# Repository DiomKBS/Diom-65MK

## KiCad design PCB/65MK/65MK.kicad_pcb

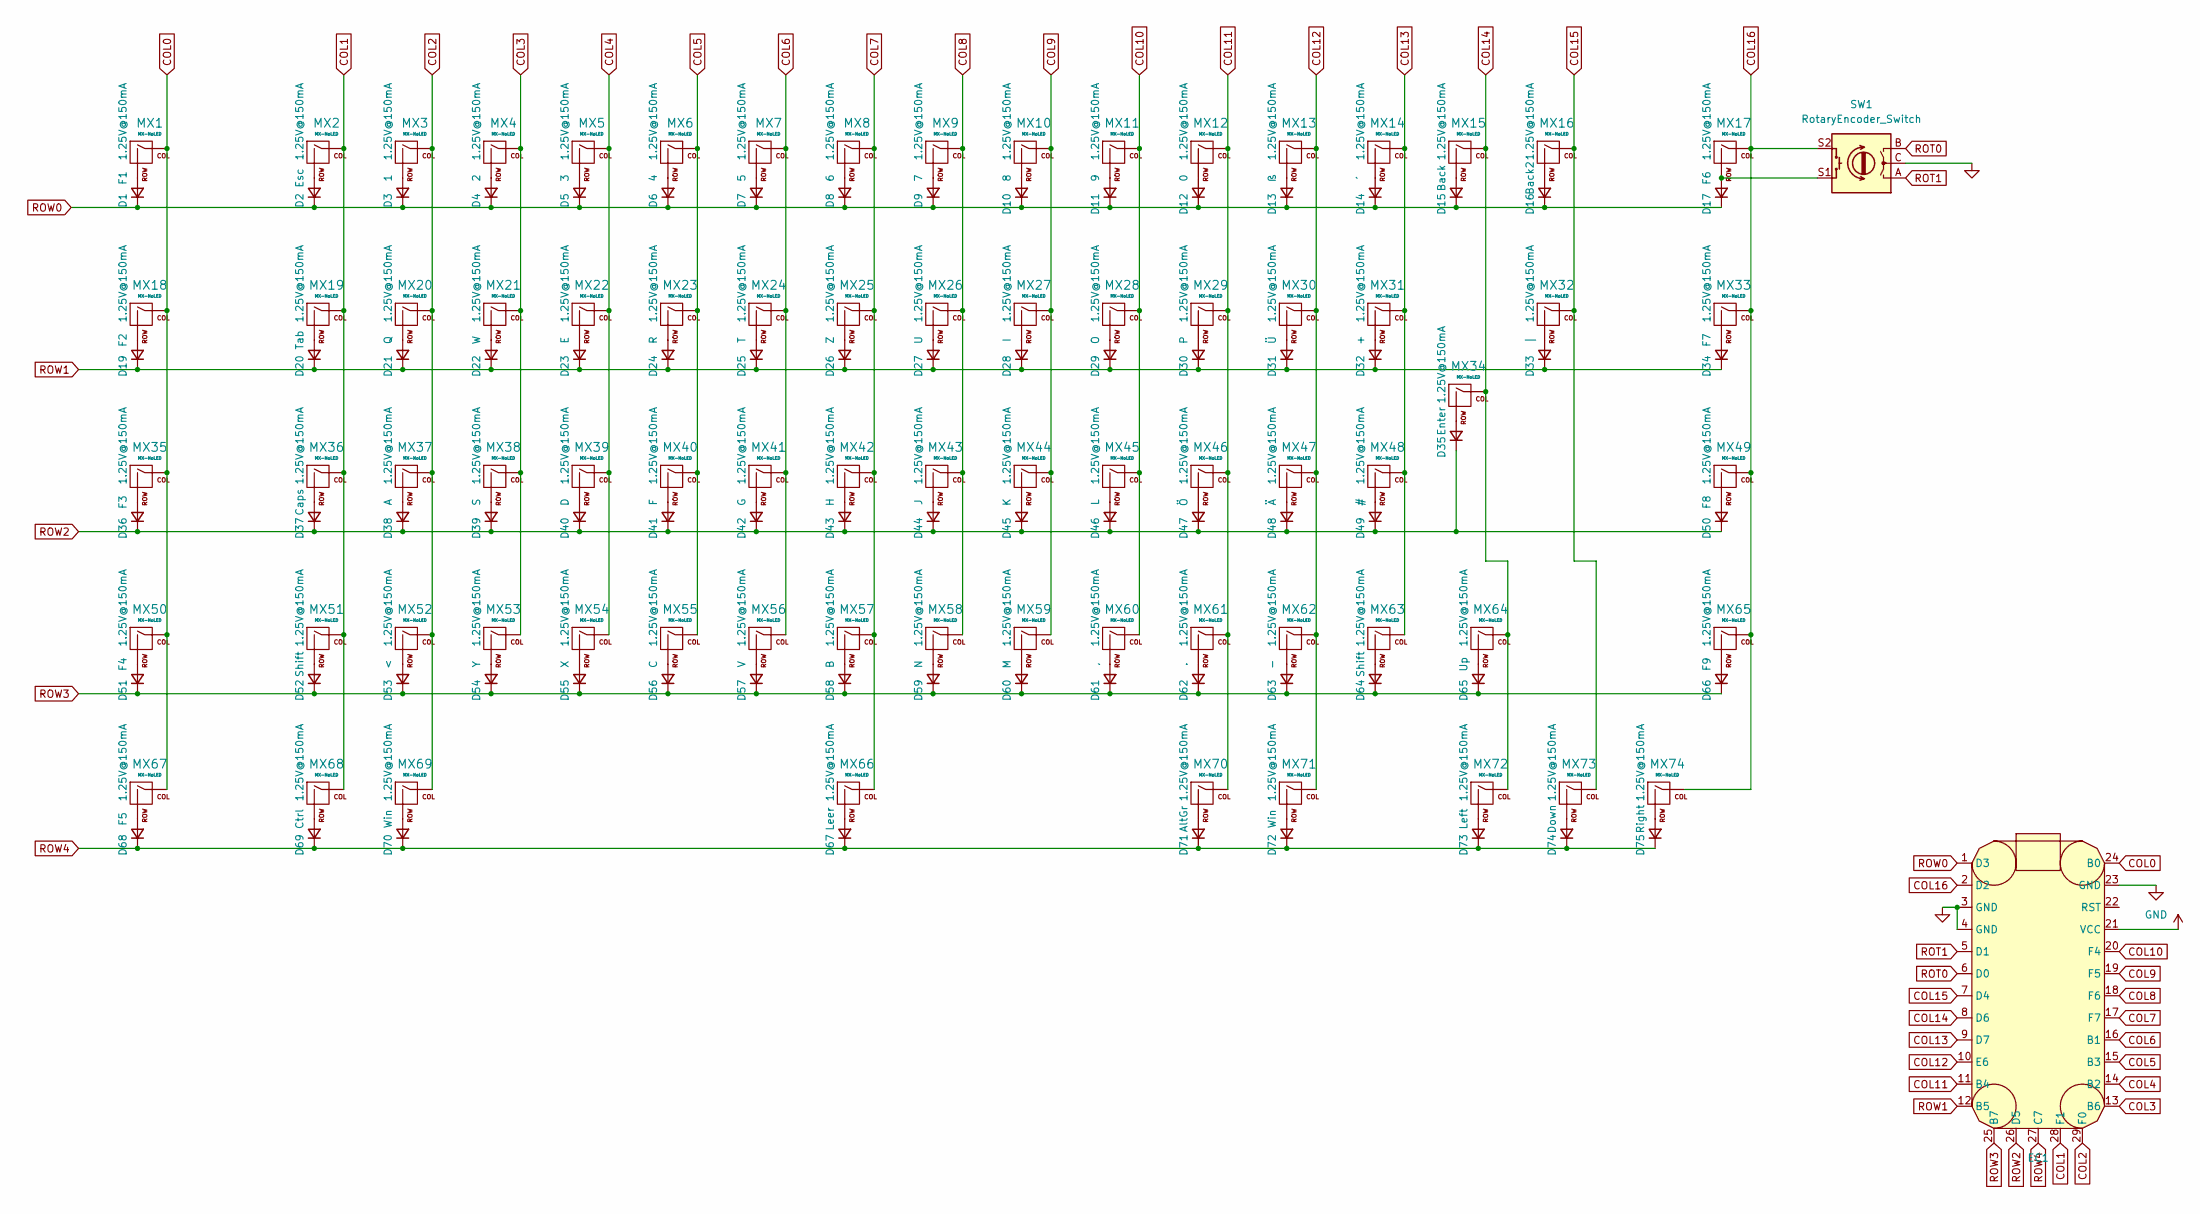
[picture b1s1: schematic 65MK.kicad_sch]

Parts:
D1, D2, D3, D4, D5, D6, D7, D8, D9, D10, D11, D12, D13, D14, D15, D16, D17, D19, D20, D21, D22, D23, D24, D25, D26, D27, D28, D29, D30, D31, D32, D33, D34, D35, D36, D37, D38, D39, D40, D41, D42, D43, D44, D45, D46, D47, D48, D49, D50, D51, D52, D53, D54, D55, D56, D57, D58, D59, D60, D61, D62, D63, D64, D65, D66, D67, D68, D69, D70, D71, D72, D73, D74, D75: 1.25V@150mA; D_SOD-123; LCSC Part C77978
EC1: (no value)
MX1, MX2, MX3, MX4, MX5, MX6, MX7, MX8, MX9, MX10, MX11, MX12, MX13, MX14, MX15, MX16, MX17, MX18, MX19, MX20, MX21, MX22, MX23, MX24, MX25, MX26, MX27, MX28, MX29, MX30, MX31, MX32, MX33, MX34, MX35, MX36, MX37, MX38, MX39, MX40, MX41, MX42, MX43, MX44, MX45, MX46, MX47, MX48, MX49, MX50, MX51, MX52, MX53, MX54, MX55, MX56, MX57, MX58, MX59, MX60, MX61, MX62, MX63, MX64, MX65, MX66, MX67, MX68, MX69, MX70, MX71, MX72, MX73, MX74: MX-NoLED
SW1: RotaryEncoder_Switch; RotaryEncoder_EC11E-Switch; LCSC Part C470754

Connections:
COL0: EC1.24 (B0), MX1.1 (COL), MX18.1 (COL), MX35.1 (COL), MX50.1 (COL), MX67.1 (COL)
COL1: EC1.28 (F1), MX2.1 (COL), MX19.1 (COL), MX36.1 (COL), MX51.1 (COL), MX68.1 (COL)
COL2: EC1.29 (F0), MX3.1 (COL), MX20.1 (COL), MX37.1 (COL), MX52.1 (COL), MX69.1 (COL)
COL3: EC1.13 (B6), MX4.1 (COL), MX21.1 (COL), MX38.1 (COL), MX53.1 (COL)
COL4: EC1.14 (B2), MX5.1 (COL), MX22.1 (COL), MX39.1 (COL), MX54.1 (COL)
COL5: EC1.15 (B3), MX6.1 (COL), MX23.1 (COL), MX40.1 (COL), MX55.1 (COL)
COL6: EC1.16 (B1), MX7.1 (COL), MX24.1 (COL), MX41.1 (COL), MX56.1 (COL)
COL7: EC1.17 (F7), MX8.1 (COL), MX25.1 (COL), MX42.1 (COL), MX57.1 (COL), MX66.1 (COL)
COL8: EC1.18 (F6), MX9.1 (COL), MX26.1 (COL), MX43.1 (COL), MX58.1 (COL)
COL9: EC1.19 (F5), MX10.1 (COL), MX27.1 (COL), MX44.1 (COL), MX59.1 (COL)
COL10: EC1.20 (F4), MX11.1 (COL), MX28.1 (COL), MX45.1 (COL), MX60.1 (COL)
COL11: EC1.11 (B4), MX12.1 (COL), MX29.1 (COL), MX46.1 (COL), MX61.1 (COL), MX70.1 (COL)
COL12: EC1.10 (E6), MX13.1 (COL), MX30.1 (COL), MX47.1 (COL), MX62.1 (COL), MX71.1 (COL)
COL13: EC1.9 (D7), MX14.1 (COL), MX31.1 (COL), MX48.1 (COL), MX63.1 (COL)
COL14: EC1.8 (D6), MX15.1 (COL), MX34.1 (COL), MX64.1 (COL), MX72.1 (COL)
COL15: EC1.7 (D4), MX16.1 (COL), MX32.1 (COL), MX73.1 (COL)
COL16: EC1.2 (D2), MX17.1 (COL), MX33.1 (COL), MX49.1 (COL), MX65.1 (COL), MX74.1 (COL), SW1.S2
unnamed: D1.2 (A), MX1.2 (ROW)
unnamed: D2.2 (A), MX2.2 (ROW)
unnamed: D3.2 (A), MX3.2 (ROW)
unnamed: D4.2 (A), MX4.2 (ROW)
unnamed: D5.2 (A), MX5.2 (ROW)
unnamed: D6.2 (A), MX6.2 (ROW)
unnamed: D7.2 (A), MX7.2 (ROW)
unnamed: D8.2 (A), MX8.2 (ROW)
unnamed: D9.2 (A), MX9.2 (ROW)
unnamed: D10.2 (A), MX10.2 (ROW)
unnamed: D11.2 (A), MX11.2 (ROW)
unnamed: D12.2 (A), MX12.2 (ROW)
unnamed: D13.2 (A), MX13.2 (ROW)
unnamed: D14.2 (A), MX14.2 (ROW)
unnamed: D15.2 (A), MX15.2 (ROW)
unnamed: D16.2 (A), MX16.2 (ROW)
unnamed: D17.2 (A), MX17.2 (ROW), SW1.S1
unnamed: D19.2 (A), MX18.2 (ROW)
unnamed: D20.2 (A), MX19.2 (ROW)
unnamed: D21.2 (A), MX20.2 (ROW)
unnamed: D22.2 (A), MX21.2 (ROW)
unnamed: D23.2 (A), MX22.2 (ROW)
unnamed: D24.2 (A), MX23.2 (ROW)
unnamed: D25.2 (A), MX24.2 (ROW)
unnamed: D26.2 (A), MX25.2 (ROW)
unnamed: D27.2 (A), MX26.2 (ROW)
unnamed: D28.2 (A), MX27.2 (ROW)
unnamed: D29.2 (A), MX28.2 (ROW)
unnamed: D30.2 (A), MX29.2 (ROW)
unnamed: D31.2 (A), MX30.2 (ROW)
unnamed: D32.2 (A), MX31.2 (ROW)
unnamed: D33.2 (A), MX32.2 (ROW)
unnamed: D34.2 (A), MX33.2 (ROW)
unnamed: D35.2 (A), MX34.2 (ROW)
unnamed: D36.2 (A), MX35.2 (ROW)
unnamed: D37.2 (A), MX36.2 (ROW)
unnamed: D38.2 (A), MX37.2 (ROW)
unnamed: D39.2 (A), MX38.2 (ROW)
unnamed: D40.2 (A), MX39.2 (ROW)
unnamed: D41.2 (A), MX40.2 (ROW)
unnamed: D42.2 (A), MX41.2 (ROW)
unnamed: D43.2 (A), MX42.2 (ROW)
unnamed: D44.2 (A), MX43.2 (ROW)
unnamed: D45.2 (A), MX44.2 (ROW)
unnamed: D46.2 (A), MX45.2 (ROW)
unnamed: D47.2 (A), MX46.2 (ROW)
unnamed: D48.2 (A), MX47.2 (ROW)
unnamed: D49.2 (A), MX48.2 (ROW)
unnamed: D50.2 (A), MX49.2 (ROW)
unnamed: D51.2 (A), MX50.2 (ROW)
unnamed: D52.2 (A), MX51.2 (ROW)
unnamed: D53.2 (A), MX52.2 (ROW)
unnamed: D54.2 (A), MX53.2 (ROW)
unnamed: D55.2 (A), MX54.2 (ROW)
unnamed: D56.2 (A), MX55.2 (ROW)
unnamed: D57.2 (A), MX56.2 (ROW)
unnamed: D58.2 (A), MX57.2 (ROW)
unnamed: D59.2 (A), MX58.2 (ROW)
unnamed: D60.2 (A), MX59.2 (ROW)
unnamed: D61.2 (A), MX60.2 (ROW)
unnamed: D62.2 (A), MX61.2 (ROW)
unnamed: D63.2 (A), MX62.2 (ROW)
unnamed: D64.2 (A), MX63.2 (ROW)
unnamed: D65.2 (A), MX64.2 (ROW)
unnamed: D66.2 (A), MX65.2 (ROW)
unnamed: D67.2 (A), MX66.2 (ROW)
unnamed: D68.2 (A), MX67.2 (ROW)
unnamed: D69.2 (A), MX68.2 (ROW)
unnamed: D70.2 (A), MX69.2 (ROW)
unnamed: D71.2 (A), MX70.2 (ROW)
unnamed: D72.2 (A), MX71.2 (ROW)
unnamed: D73.2 (A), MX72.2 (ROW)
unnamed: D74.2 (A), MX73.2 (ROW)
unnamed: D75.2 (A), MX74.2 (ROW)
ROT0: EC1.6 (D0), SW1.B
ROT1: EC1.5 (D1), SW1.A
ROW0: D1.1 (K), D2.1 (K), D3.1 (K), D4.1 (K), D5.1 (K), D6.1 (K), D7.1 (K), D8.1 (K), D9.1 (K), D10.1 (K), D11.1 (K), D12.1 (K), D13.1 (K), D14.1 (K), D15.1 (K), D16.1 (K), D17.1 (K), EC1.1 (D3)
ROW1: D19.1 (K), D20.1 (K), D21.1 (K), D22.1 (K), D23.1 (K), D24.1 (K), D25.1 (K), D26.1 (K), D27.1 (K), D28.1 (K), D29.1 (K), D30.1 (K), D31.1 (K), D32.1 (K), D33.1 (K), D34.1 (K), EC1.12 (B5)
ROW2: D35.1 (K), D36.1 (K), D37.1 (K), D38.1 (K), D39.1 (K), D40.1 (K), D41.1 (K), D42.1 (K), D43.1 (K), D44.1 (K), D45.1 (K), D46.1 (K), D47.1 (K), D48.1 (K), D49.1 (K), D50.1 (K), EC1.26 (D5)
ROW3: D51.1 (K), D52.1 (K), D53.1 (K), D54.1 (K), D55.1 (K), D56.1 (K), D57.1 (K), D58.1 (K), D59.1 (K), D60.1 (K), D61.1 (K), D62.1 (K), D63.1 (K), D64.1 (K), D65.1 (K), D66.1 (K), EC1.25 (B7)
ROW4: D67.1 (K), D68.1 (K), D69.1 (K), D70.1 (K), D71.1 (K), D72.1 (K), D73.1 (K), D74.1 (K), D75.1 (K), EC1.27 (C7)

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
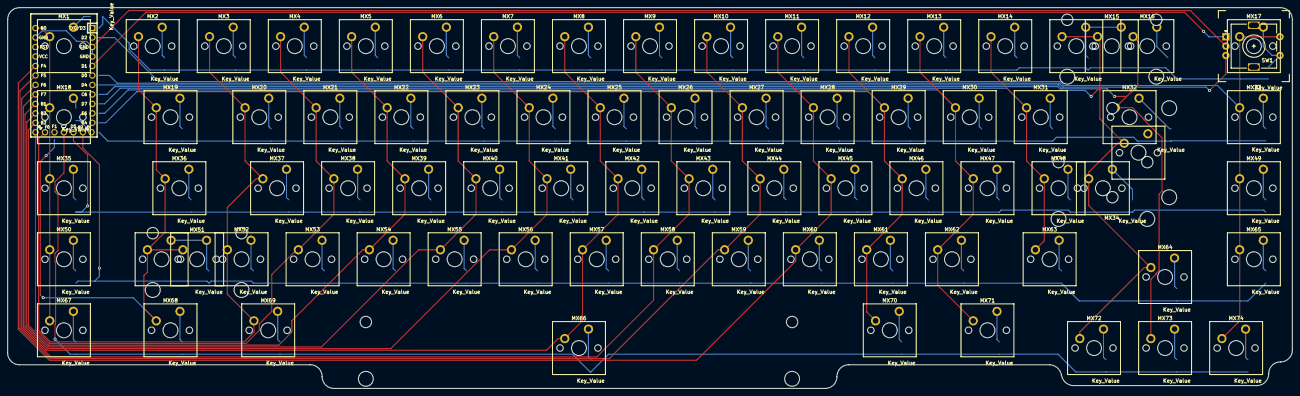
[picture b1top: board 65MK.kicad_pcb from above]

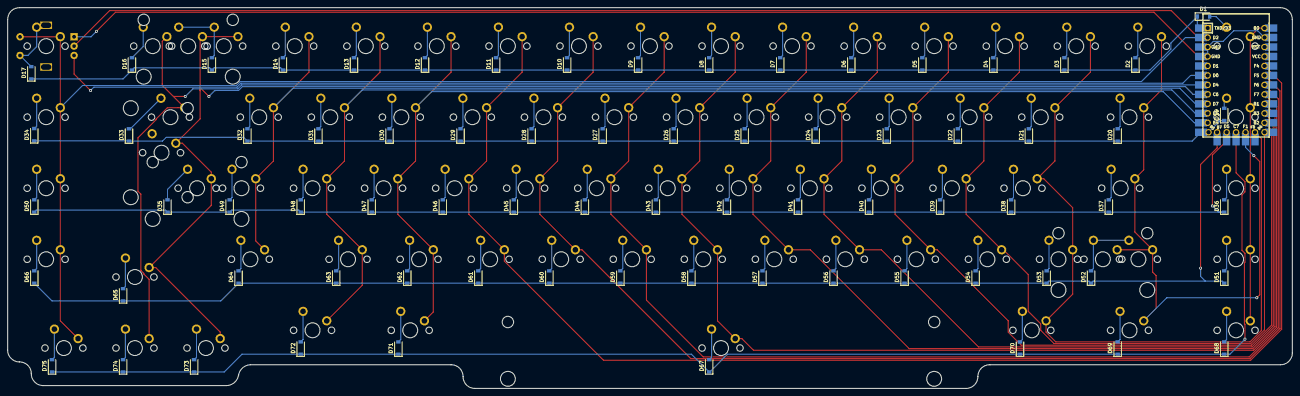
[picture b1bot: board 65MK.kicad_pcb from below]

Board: 2 copper layers, 344.5 x 102.1 mm, 150 parts (75 on the bottom side), 99 nets.

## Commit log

2022-07-27 Schematic and Board finished
    Maybe some fixes needed
2022-08-01 3d Models
2022-11-05 Added Gerbers
2023-04-17 added step models
